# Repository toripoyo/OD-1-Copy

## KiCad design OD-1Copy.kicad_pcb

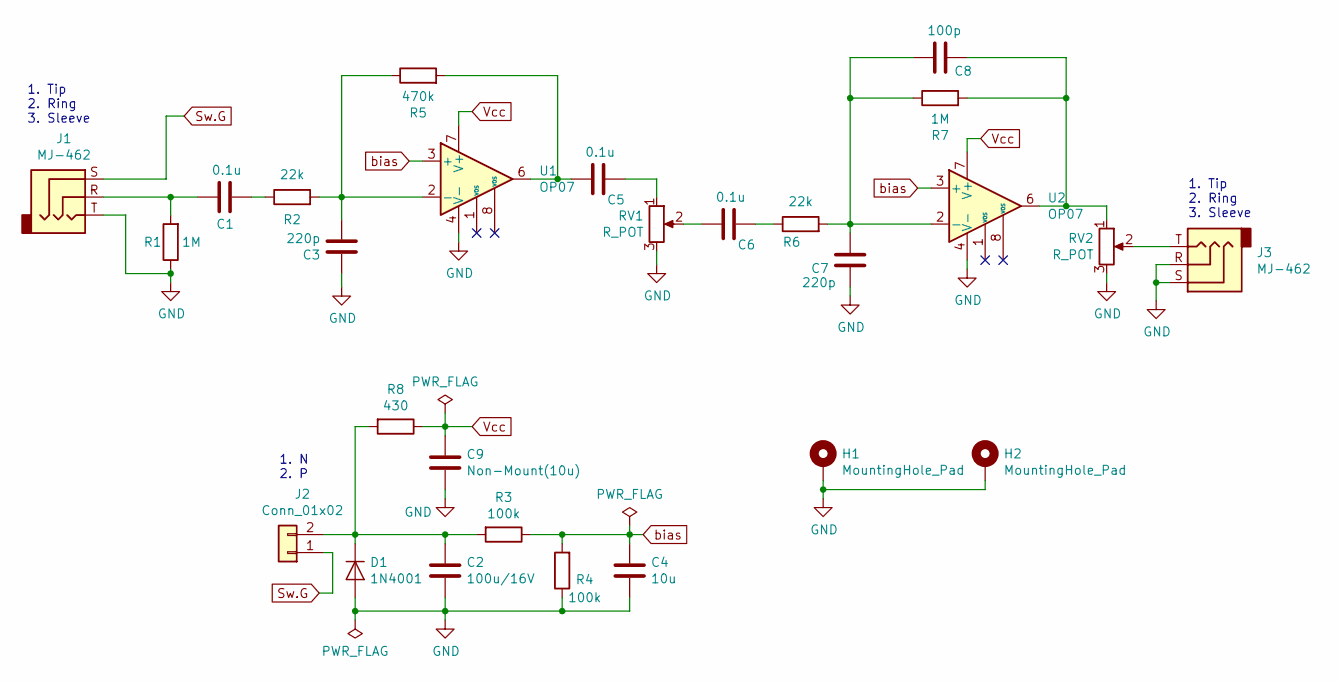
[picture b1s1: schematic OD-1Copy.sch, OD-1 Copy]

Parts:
C1, C5, C6: 0.1u; C_0805_2012Metric_Pad1.15x1.50mm_HandSolder
C2: 100u/16V; CP_Radial_D5.0mm_P2.50mm
C3, C7: 220p; C_0805_2012Metric_Pad1.15x1.50mm_HandSolder
C4: 10u; C_0805_2012Metric_Pad1.15x1.50mm_HandSolder
C8: 100p; C_0805_2012Metric_Pad1.15x1.50mm_HandSolder
C9: Non-Mount(10u); C_0805_2012Metric_Pad1.15x1.50mm_HandSolder
D1: 1N4001; D_A-405_P2.54mm_Vertical_KathodeUp
H1, H2: MountingHole_Pad; MountingHole_3.2mm_M3_Pad
J1, J3: MJ-462; Jack_3.5mm_Neutrik_NMJ6HCD2_Horizontal
J2: Conn_01x02; PinHeader_1x02_P2.54mm_Vertical
R1, R7: 1M; C_0805_2012Metric_Pad1.15x1.50mm_HandSolder
R2, R6: 22k; C_0805_2012Metric_Pad1.15x1.50mm_HandSolder
R3, R4: 100k; C_0805_2012Metric_Pad1.15x1.50mm_HandSolder
R5: 470k; C_0805_2012Metric_Pad1.15x1.50mm_HandSolder
R8: 430; C_0805_2012Metric_Pad1.15x1.50mm_HandSolder
RV1, RV2: R_POT; PinHeader_1x03_P2.54mm_Vertical
U1, U2: OP07; DIP-8_W7.62mm

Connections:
GND: C2.2, C3.1, C4.2, C7.1, C9.2, D1.2 (A), H1.1, H2.1, J1.T, J3.R, J3.S, R1.1, R4.1, RV1.3, RV2.3, U1.4 (V-), U2.4 (V-)
unnamed: C1.1, R2.1
unnamed: C1.2, J1.R, R1.2
unnamed: C2.1, D1.1 (K), J2.2, R3.2, R8.2
unnamed: C3.2, R2.2, R5.1, U1.2 (-)
unnamed: C5.1, RV1.1
unnamed: C5.2, R5.2, U1.6
unnamed: C6.1, R6.1
unnamed: C6.2, RV1.2
unnamed: C7.2, C8.2, R6.2, R7.1, U2.2 (-)
unnamed: C8.1, R7.2, RV2.1, U2.6
unnamed: J3.T, RV2.2
Sw.G: J1.S, J2.1
Vcc: C9.1, R8.1, U1.7 (V+), U2.7 (V+)
bias: C4.1, R3.1, R4.2, U1.3 (+), U2.3 (+)

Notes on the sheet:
1. Tip 2. Ring 3. Sleeve
1. N 2. P

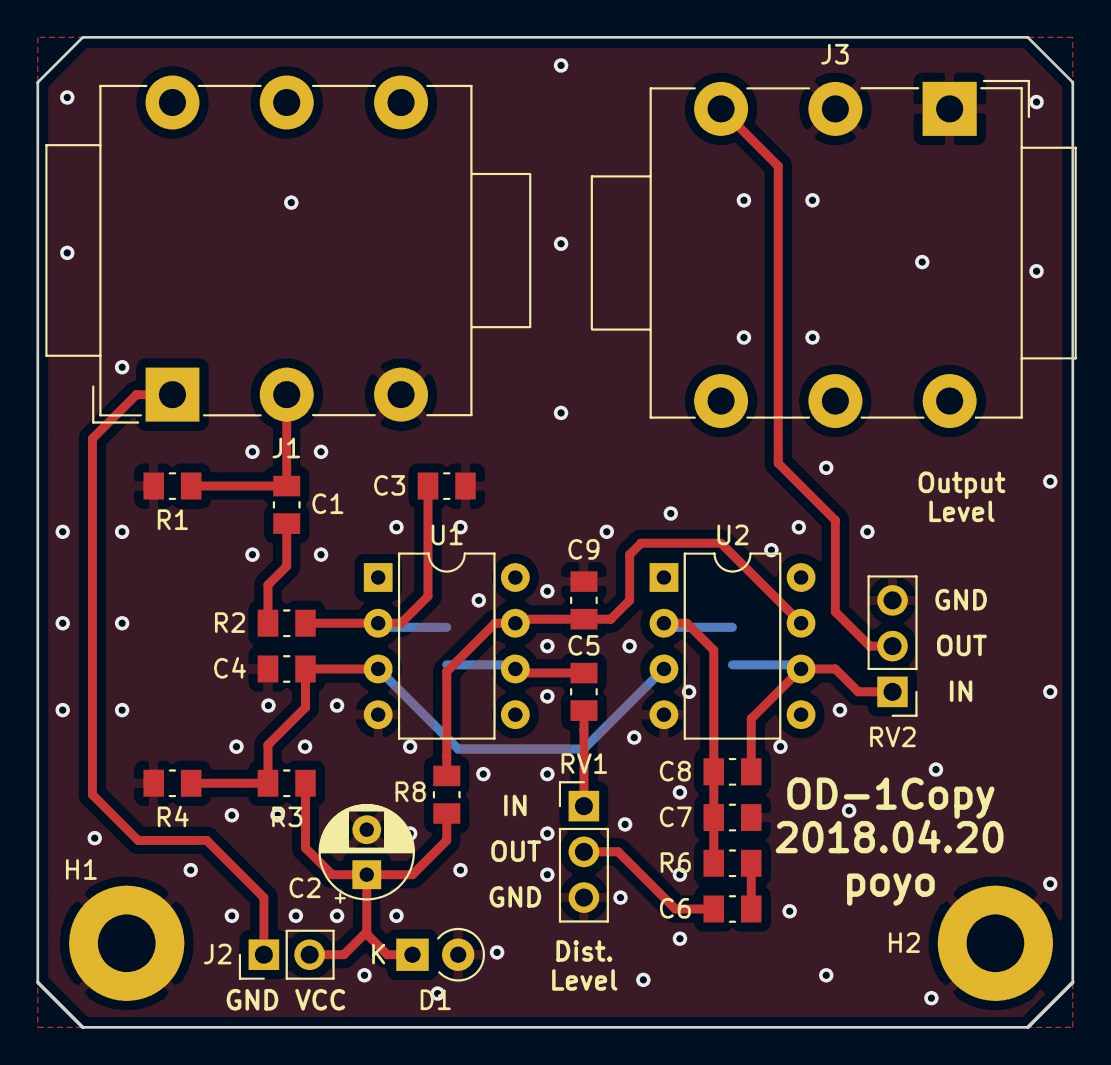
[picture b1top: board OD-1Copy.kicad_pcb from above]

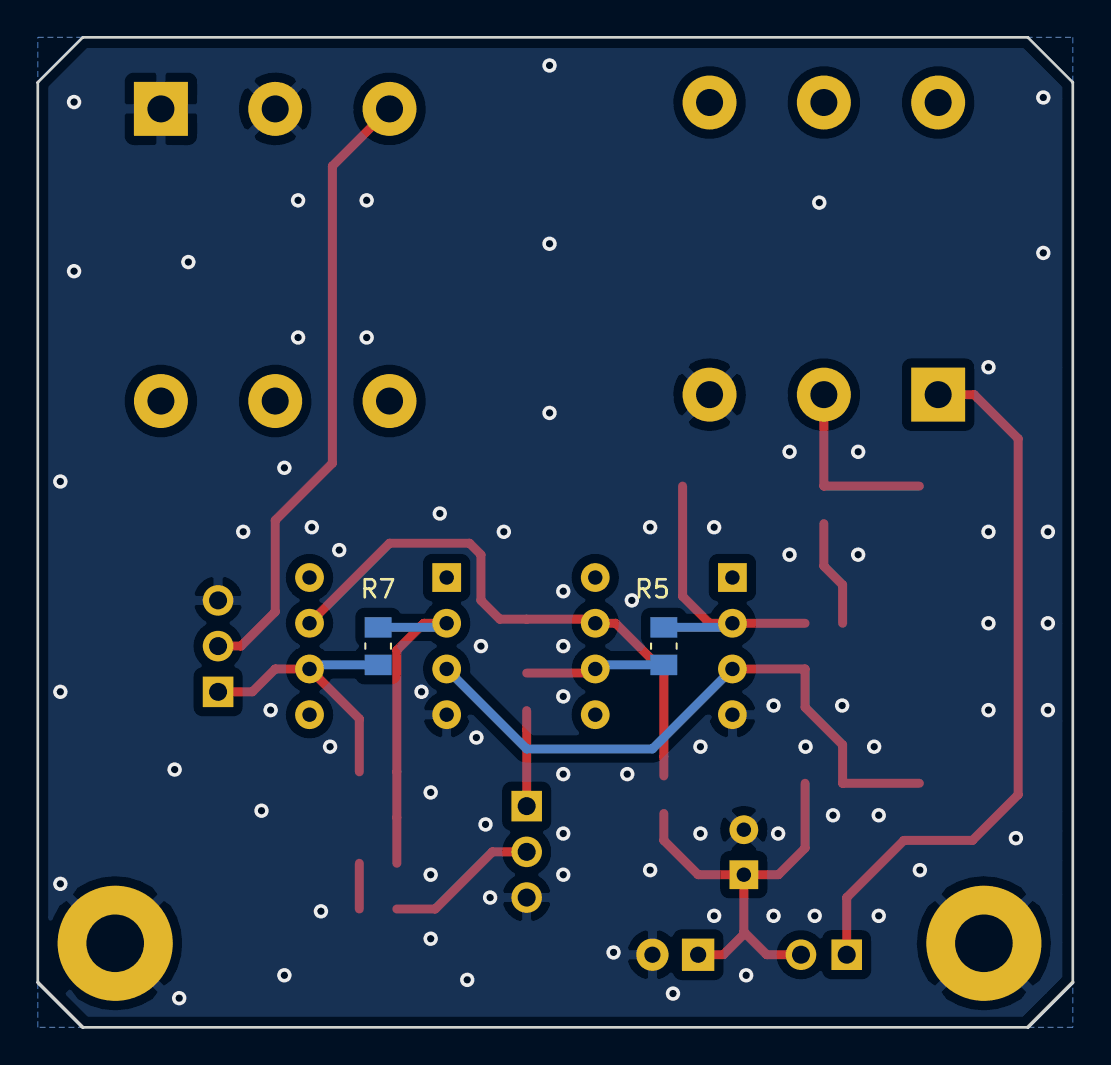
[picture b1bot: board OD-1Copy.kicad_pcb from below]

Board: 2 copper layers, 57.5 x 55.0 mm, 27 parts (2 on the bottom side), 15 nets.

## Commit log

2019-12-30 公開用に整理
